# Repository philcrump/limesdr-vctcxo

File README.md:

# limesdr-vctcxo

This PCB provides an external, thermally separate, TCXO Frequency Reference to the LimeSDR-mini board.

I built this as even though the onboard TCXO is well-specced, being next to the high-power FPGA & RF components was causing noticeable thermal drift, especially in amplitude-modulated (eg. SSB) outdoor use.

This board uses a 40MHz TCXO to be a plug-in replacement with no reconfiguration. A 12-turn potentiometer allows easy manual calibration.

[Schematic PDF file](https://github.com/philcrump/limesdr-vctcxo/raw/master/vctcxo-ref.pdf)

## PCB Images

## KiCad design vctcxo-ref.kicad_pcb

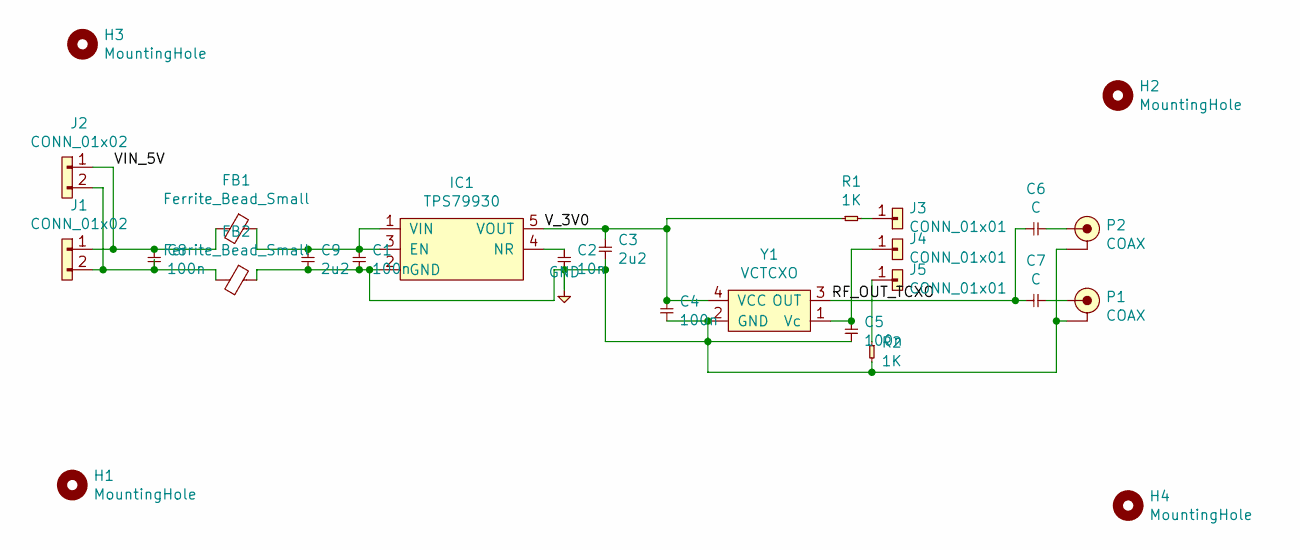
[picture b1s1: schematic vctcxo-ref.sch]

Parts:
C1, C4, C5, C8: 100n; 0603
C2: 10n; 0402
C3, C9: 2u2; 0603
C6, C7: C; 0603
FB1, FB2: Ferrite_Bead_Small; 0603
H1, H2, H3, H4: MountingHole; M3_MOUNT
IC1: TPS79930; SOT-23-5; Farnell 1135402
J1, J2: CONN_01x02; MOLEX-KK-254P-02
J3, J4, J5: CONN_01x01; TestPoint_THTPad_D1.5mm_Drill0.7mm
P1, P2: COAX; SMA-EDGE; Farnell 1608592
R1, R2: 1K; 0603
Y1: VCTCXO; XO-50x32; Farnell 2467929

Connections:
/RF_OUT_TCXO: C6.1, C7.1, Y1.3 (OUT)
/VIN_5V: C8.1, FB1.2, J1.1, J2.1
/V_3V0: C3.2, C4.2, IC1.5 (VOUT), R1.1, Y1.4 (VCC)
GND: C1.2, C2.2, C3.1, C4.1, C5.2, C9.1, FB2.1, IC1.2 (GND), P1.2 (GND), P2.2 (GND), R2.2, Y1.2 (GND)
unnamed: C1.1, C9.2, FB1.1, IC1.1 (VIN), IC1.3 (EN)
unnamed: C2.1, IC1.4 (NR)
unnamed: C5.1, J4.1, Y1.1 (Vc)
unnamed: C6.2, P2.1 (RF)
unnamed: C7.2, P1.1 (RF)
unnamed: C8.2, FB2.2, J1.2, J2.2
unnamed: J3.1, R1.2
unnamed: J5.1, R2.1

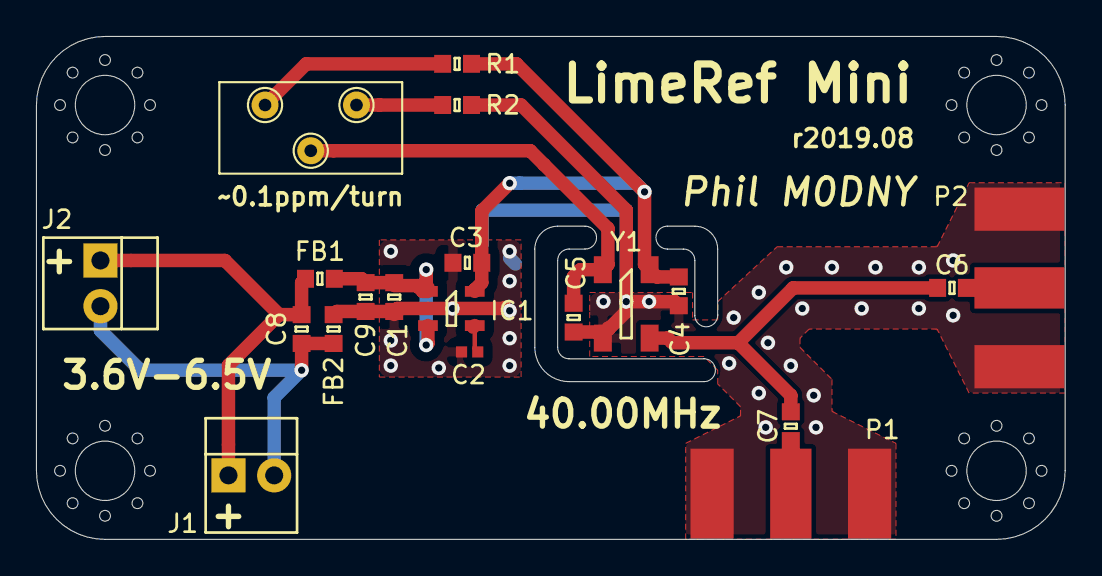
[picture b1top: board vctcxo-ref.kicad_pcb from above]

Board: 2 copper layers, 57.2 x 27.9 mm, 26 parts (0 on the bottom side), 12 nets.

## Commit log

2019-08-04 Update.
2019-08-05 lib/agg-kicad/: Fix submodule upstream (point to philcrump/ repo).
2019-08-05 Tweaks.
2019-08-19 Initial plot run.
2019-08-20 Sent to fab.
2019-12-28 Commit the BOM.
2019-12-28 Add schematic and pcb renders.
2019-12-28 Add LICENSE.
2019-12-28 Add README
2019-12-29 Add photo.
2019-12-29 README: Add photo.
